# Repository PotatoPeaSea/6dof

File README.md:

# 6dofPCB — Virtual Flux (Product Requirements & Overview)

## 1. Product Vision
**Virtual Flux** is a high-fidelity, hardware-in-the-loop soldering simulator. It bridges physical motion and virtual physics to create a realistic training and evaluation environment for hand soldering. By using a physical 6DOF (Six Degrees of Freedom) robotic arm that acts as the soldering iron (currently in development, with full keyboard/mouse fallbacks available now), users can practice their technique on a virtual PCB rendered in a Unity desktop application. The simulation provides deterministic, physics-based reactions—including thermodynamics, flux activation, and solder wetting—coupled with real-time evaluation.

## 2. Target Audience & Use Cases
- **Soldering Trainees & Students**: Learn proper technique (angle, dwell time, temperature control, flux application) without consuming physical consumables or risking damage to expensive boards.
- **Instructors & Evaluators**: Provide standardized, objective, and deterministic grading of a student's soldering joints.
- **Hardware Enthusiasts**: Experiment with a novel hardware-software interface.

## 3. Core Features & Requirements (V1)

### 3.1 Physics & Simulation Engine
The core of Virtual Flux is its deterministic, grid-based simulation running at a fixed 5 ms timestep in Unity.
- **Thermal Model**: Heuristic exponential heat transfer from the iron tip to the pad, propagating across a grid.
- **Flux Dynamics**: Tracks states of flux (Cold -> Active -> Burnt) based on temperature thresholds. Flux cleans oxidation and enables solder flow.
- **Solder Flow & Wetting**: Grid-based solder deposition that flows to heated cells. Features visual metallic rendering and dynamic fillet capillary action morphing towards component pins.
- **Component Bonding**: Solderable pins detect solid vs. molten solder. A wetting reflow state machine ensures pins only bond if they contact molten solder that subsequently cools and solidifies.

### 3.2 User Interaction & Tooling
While the physical arm is the primary input, V1 supports full keyboard/mouse fallbacks.
- **6DOF Iron**: Translates and rotates in 3D space. Reports tip temperature and spatial pose.
- **Toolbelt**:
  - **Solder Wire**: Click-to-feed solder deposition.
  - **Flux Pen / Paste**: Apply flux to pads prior to heating.
  - **Tweezers**: Drag-and-drop SMD component placement (e.g., resistors) with snap-to-surface raycasting and kinematic stability.

### 3.3 Evaluation & HUD
- **Real-Time Guidance**: Dynamic UI panel tracking the active pad. Displays a collapsing step-by-step checklist (placement, flux, heat, solder, cool).
- **Deterministic Scoring**: Evaluates the joint based on strict tolerances:
  - Soldering angle (e.g., 40–55°)
  - Dwell time (e.g., 1.5–3 s)
  - Peak temperature (e.g., 250–360 °C)
  - Flux sequence (must flux before heating)
  - Solder volume and tip-feeding requirements.
- **Status & Latency**: Heads-up displays for iron temperature, active tool, board security status, and simulation frame timing.

## 4. System Architecture

The project is split into three tightly coupled domains:

### 4.1 Hardware (KiCad)
The physical 6DOF arm is driven by custom PCBs.
- **MCU Board**: The brains of the arm.
- **Controller Board**: Interfacing and power.
- *Located in `Hardware/` as KiCad 7+ projects and RS-274X Gerbers.*

### 4.2 Firmware (C/C++)
- **PlatformIO Project**: Runs on the MCU board. Solves arm kinematics and streams the tool tip's pose and temperature over USB-serial to the PC.
- *Located in `Firmware/6DoF Firmware/` (currently in progress).*
- *Protocol locked and documented in `docs/serial-protocol.md`.*

### 4.3 Software (Unity)
- **Unity 6 LTS (6000.0.x)** using the Universal Render Pipeline (URP) and the New Input System.
- Receives serial pose data (`P,x,y,z,pitch,yaw,roll,temp,seq`) and applies it to the virtual iron.
- Parses real Gerber files to generate the virtual copper PCB meshes.
- *Located in `Software/`.*

## 5. Repository Layout

| Path                | Contents                                                          |
|---------------------|-------------------------------------------------------------------|
| `Hardware/MCU/`     | MCU board — KiCad project + Gerbers. Lives on the arm itself.     |
| `Hardware/Controller/` | Controller board — KiCad project + Gerbers.                    |
| `Hardware/Gerbers/` | Zipped Gerber bundles for fabrication.                            |
| `Hardware/assets.pretty/` | Shared KiCad footprint library.                             |
| `Firmware/`         | PlatformIO firmware project for the 6DOF arm.                     |
| `Software/`         | Unity 6 LTS project. Open this folder in Unity Hub.               |
| `docs/`             | Cross-cutting docs — start with `serial-protocol.md`.             |
| `CLAUDE.md`         | Working agreement for AI coding assistants.                       |
| `NOTES.md`          | Session handoff log & historical milestones.                      |

## 6. Quick Start

1. **Hardware**: Open `Hardware/MCU/MCU.kicad_pro` or `Hardware/Controller/Controller.kicad_pro` in KiCad 7+.
2. **Software**: Open `Software/` in Unity 6 LTS. Load `Assets/Scenes/Workbench.unity` and press Play. See `Software/README.md` for detailed keyboard/mouse controls.

## 7. Future Roadmap (Post-V1)

- **Arm Firmware Completion**: Finish the C/C++ kinematics solver and hardware integration.
- **AI Joint-Quality Evaluation**: Machine learning models to assess the visual quality of the final solder fillet.
- **Advanced Hardware**: Haptic feedback, VR integration, and BLE wireless connectivity.

## License
TBD.

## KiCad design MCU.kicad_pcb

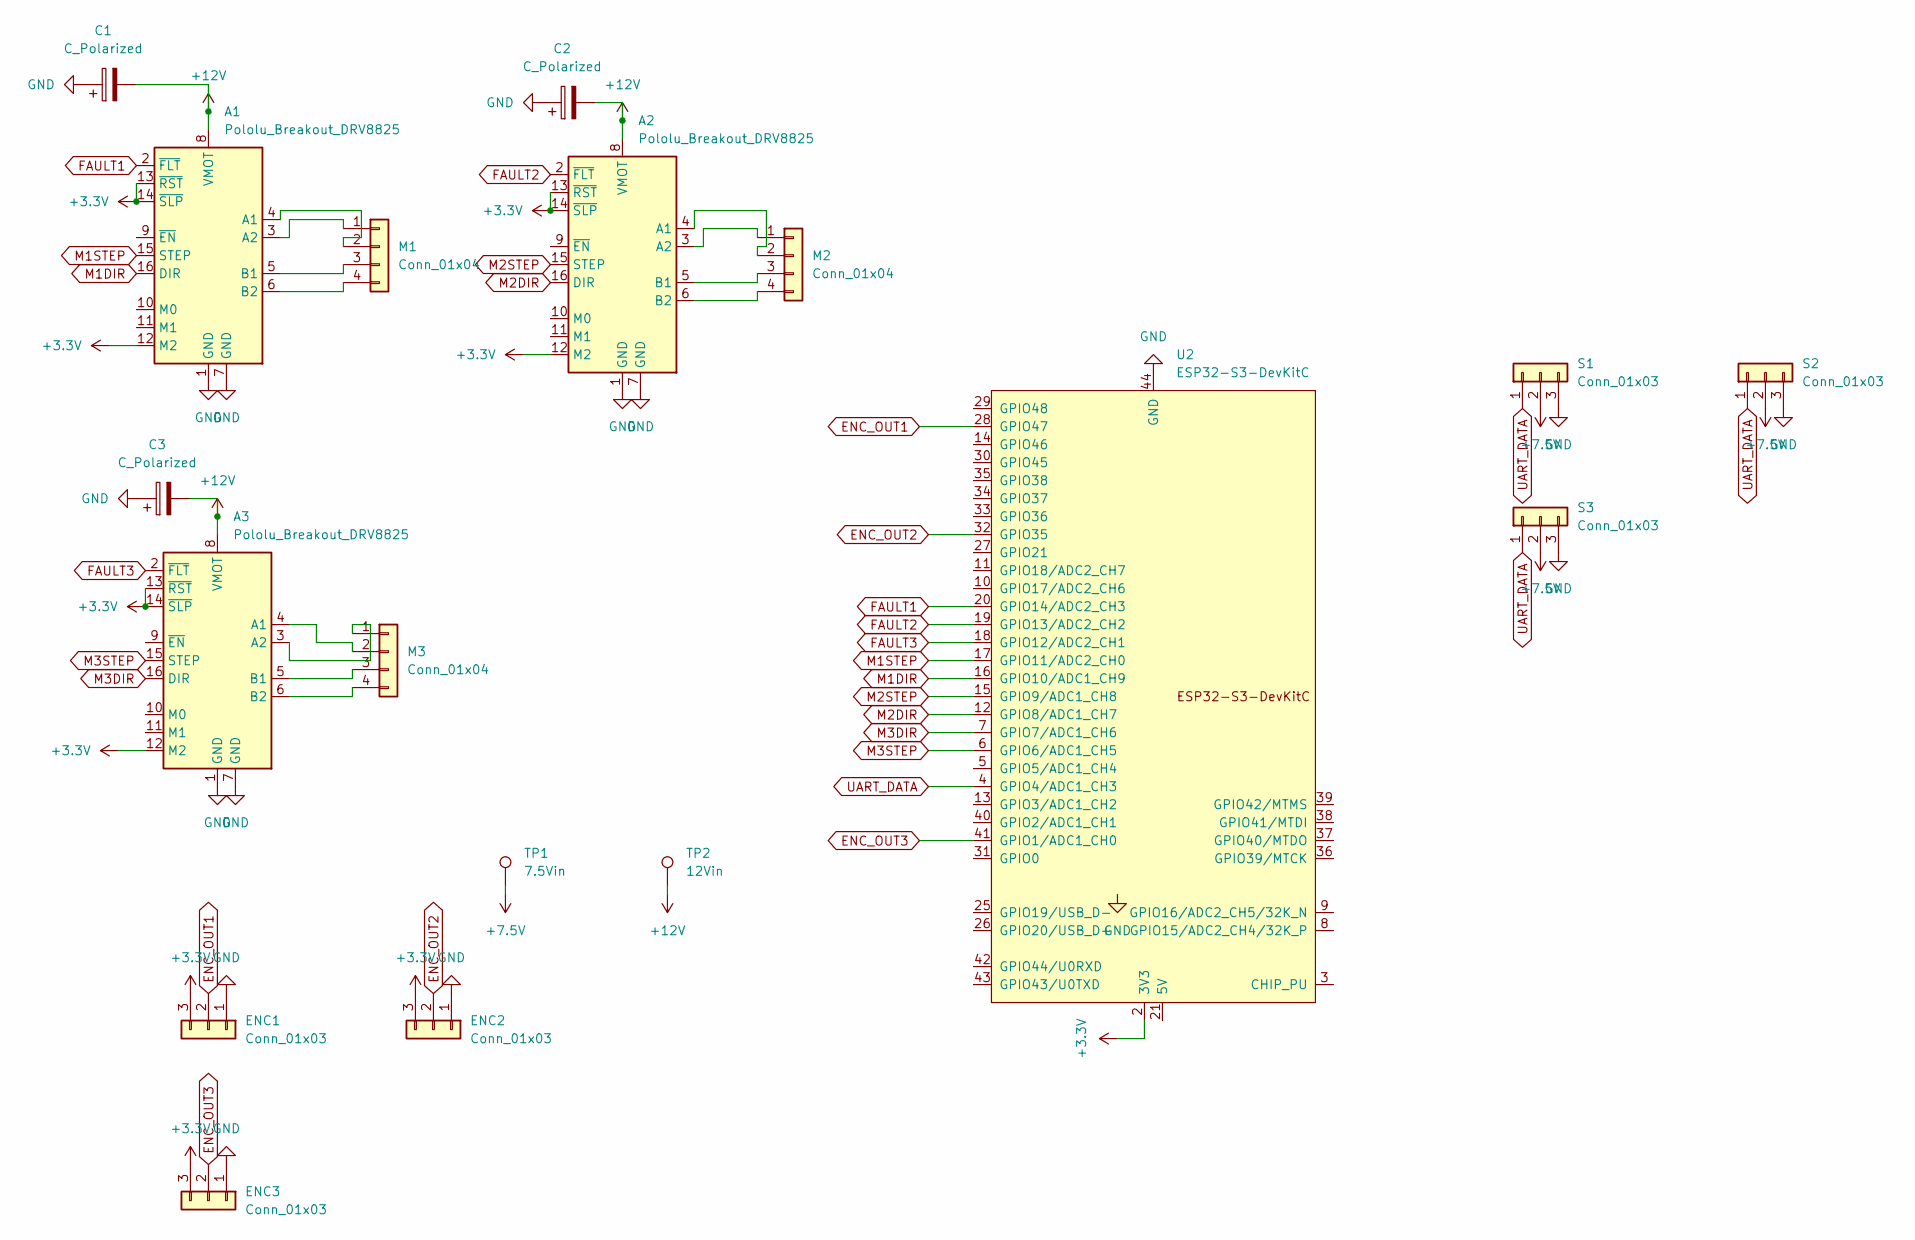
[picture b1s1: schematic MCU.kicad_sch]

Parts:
A1, A2, A3: Pololu_Breakout_DRV8825; Pololu_Breakout-16_15.2x20.3mm
C1, C2, C3: C_Polarized; CP_Radial_D6.3mm_P2.50mm
ENC1, ENC2, ENC3: Conn_01x03; PinHeader_1x03_P2.54mm_Vertical
M1, M2, M3: Conn_01x04; PinHeader_1x04_P2.54mm_Vertical
S1, S2, S3: Conn_01x03; JST_EH_B3B-EH-A_1x03_P2.50mm_Vertical
TP1: 7.5Vin; TestPoint_Plated_Hole_D5.0mm
TP2: 12Vin; TestPoint_Plated_Hole_D5.0mm
U2: ESP32-S3-DevKitC

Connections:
+3.3V: A1.12 (M2), A1.13 (~RST), A1.14 (~SLP), A2.12 (M2), A2.13 (~RST), A2.14 (~SLP), A3.12 (M2), A3.13 (~RST), A3.14 (~SLP), ENC1.3, ENC2.3, ENC3.3, U2.1 (3V3), U2.2 (3V3)
+7.5V: S1.2, S2.2, S3.2, TP1.1 (1_1)
+12V: A1.8 (VMOT), A2.8 (VMOT), A3.8 (VMOT), C1.2, C2.2, C3.2, TP2.1 (1_1)
ENC_OUT1: ENC1.2, U2.28 (GPIO47)
ENC_OUT2: ENC2.2, U2.32 (GPIO35)
ENC_OUT3: ENC3.2, U2.41 (GPIO1/ADC1_CH0)
FAULT1: A1.2 (~FLT), U2.20 (GPIO14/ADC2_CH3)
FAULT2: A2.2 (~FLT), U2.19 (GPIO13/ADC2_CH2)
FAULT3: A3.2 (~FLT), U2.18 (GPIO12/ADC2_CH1)
GND: A1.1 (GND), A1.7 (GND), A2.1 (GND), A2.7 (GND), A3.1 (GND), A3.7 (GND), C1.1, C2.1, C3.1, ENC1.1, ENC2.1, ENC3.1, S1.3, S2.3, S3.3, U2.22 (GND), U2.23 (GND), U2.24 (GND), U2.44 (GND)
M1DIR: A1.16 (DIR), U2.16 (GPIO10/ADC1_CH9)
M1STEP: A1.15 (STEP), U2.17 (GPIO11/ADC2_CH0)
M2DIR: A2.16 (DIR), U2.12 (GPIO8/ADC1_CH7)
M2STEP: A2.15 (STEP), U2.15 (GPIO9/ADC1_CH8)
M3DIR: A3.16 (DIR), U2.7 (GPIO7/ADC1_CH6)
M3STEP: A3.15 (STEP), U2.6 (GPIO6/ADC1_CH5)
unnamed: A1.4 (A1), M1.2
unnamed: A1.3 (A2), M1.1
unnamed: A1.5 (B1), M1.3
unnamed: A1.6 (B2), M1.4
unnamed: A2.4 (A1), M2.2
unnamed: A2.3 (A2), M2.1
unnamed: A2.5 (B1), M2.3
unnamed: A2.6 (B2), M2.4
unnamed: A3.4 (A1), M3.2
unnamed: A3.3 (A2), M3.1
unnamed: A3.5 (B1), M3.3
unnamed: A3.6 (B2), M3.4
UART_DATA: S1.1, S2.1, S3.1, U2.4 (GPIO4/ADC1_CH3)

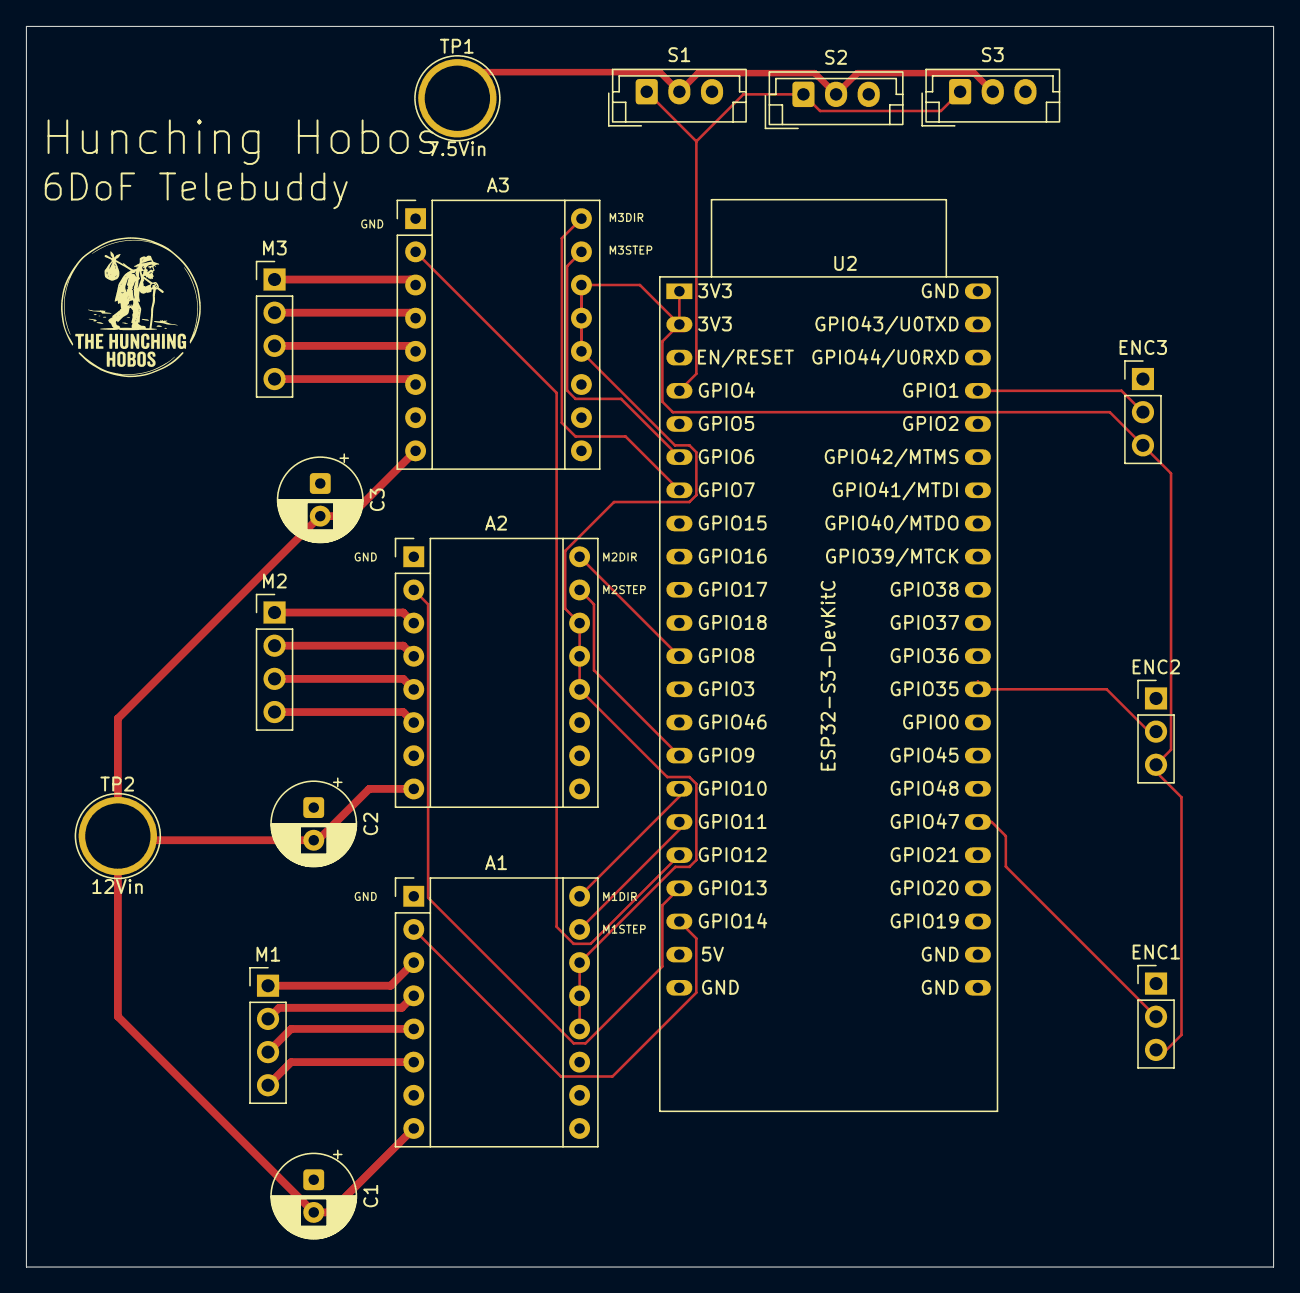
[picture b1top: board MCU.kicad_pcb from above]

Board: 2 copper layers, 95.5 x 95.0 mm, 18 parts (0 on the bottom side), 29 nets.

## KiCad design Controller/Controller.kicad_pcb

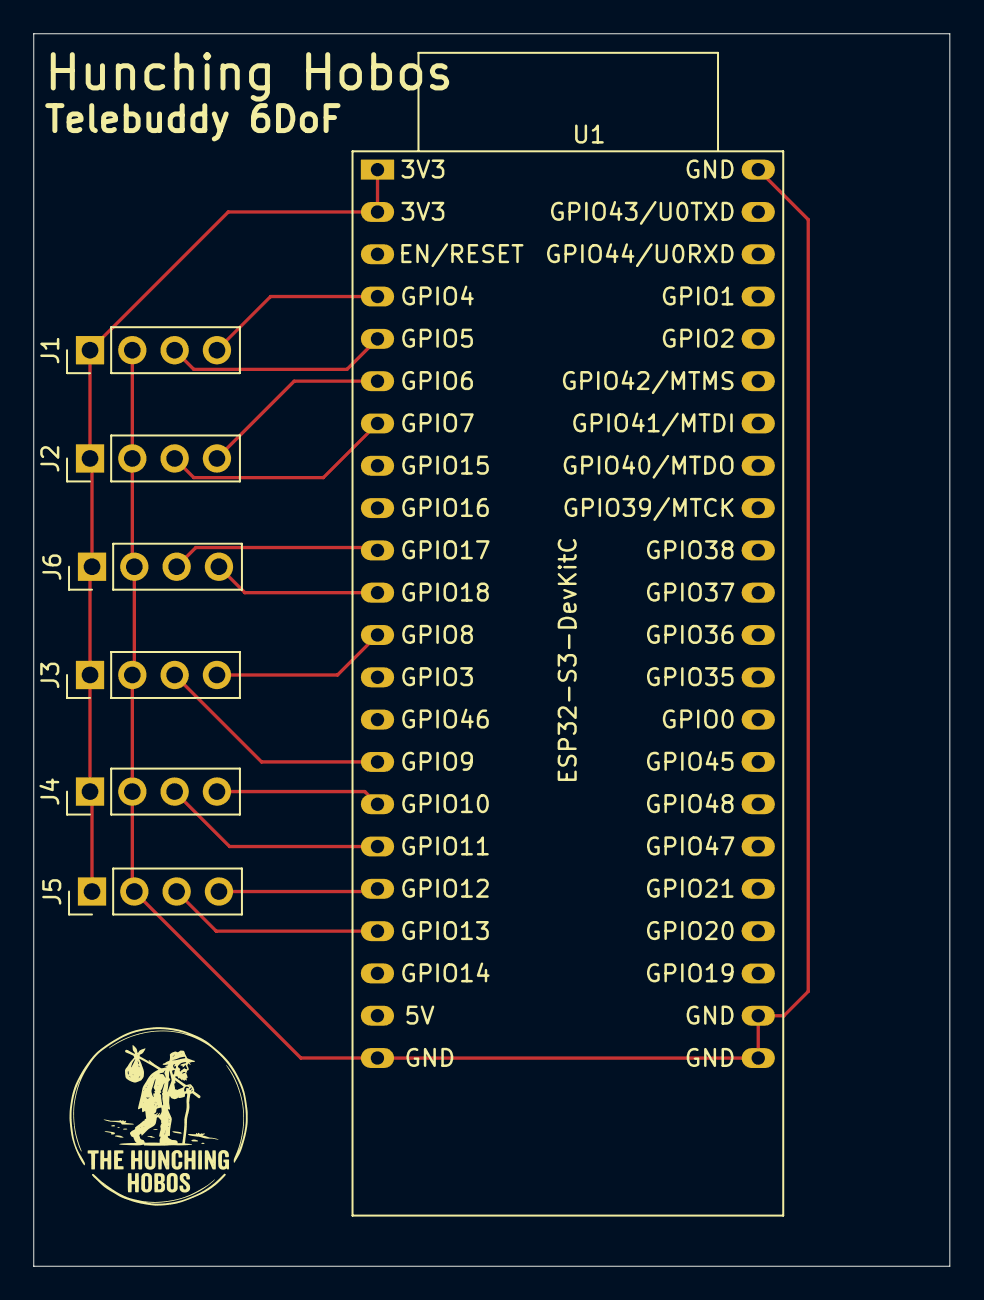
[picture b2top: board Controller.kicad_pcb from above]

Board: 2 copper layers, 55.0 x 74.0 mm, 7 parts (0 on the bottom side), 14 nets.

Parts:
J1, J2, J3, J4, J5, J6: Conn_01x04; PinHeader_1x04_P2.54mm_Vertical
U1: ESP32-S3-DevKitC

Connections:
+3.3V: J1.1, J2.1, J3.1, J4.1, J5.1, J6.1, U1.1 (3V3), U1.2 (3V3)
GND: J1.2, J2.2, J3.2, J4.2, J5.2, J6.2, U1.22 (GND), U1.23 (GND), U1.24 (GND), U1.44 (GND)
SCL1: J1.3, U1.5 (GPIO5/ADC1_CH4)
SCL2: J2.3, U1.7 (GPIO7/ADC1_CH6)
SCL3: J3.3, U1.15 (GPIO9/ADC1_CH8)
SCL4: J4.3, U1.17 (GPIO11/ADC2_CH0)
SCL5: J5.3, U1.19 (GPIO13/ADC2_CH2)
SCL6: J6.3, U1.10 (GPIO17/ADC2_CH6)
SDA1: J1.4, U1.4 (GPIO4/ADC1_CH3)
SDA2: J2.4, U1.6 (GPIO6/ADC1_CH5)
SDA3: J3.4, U1.12 (GPIO8/ADC1_CH7)
SDA4: J4.4, U1.16 (GPIO10/ADC1_CH9)
SDA5: J5.4, U1.18 (GPIO12/ADC2_CH1)
SDA6: J6.4, U1.11 (GPIO18/ADC2_CH7)

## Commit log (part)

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2026-05-26 Changed routings and added encoder ports (pwm output pins).
2026-05-26 finished trace wiring on PCB
2026-05-26 fixed trace widths
2026-05-27 completed board, ready for review, if passes review, ready to print
2026-05-27 forgot to add these
2026-05-27 changed logo footprint and capacitor spacing and labels
2026-05-27 created controller board and generated gerber files
2026-05-27 chore: restructure repo into Hardware/ + prep Software/ sibling
    Move all PCB sources (MCU project, Controller project, Gerbers, assets.pretty
    footprint library) under Hardware/. fp-lib-table relocated to Hardware/MCU/
    to preserve KiCad's "project-local table next to .kicad_pro" lookup, since
    the original layout had it next to the MCU project at root.
    Add Hardware/Firmware/ placeholder, top-level README.md, CLAUDE.md working
    agreement, and update .gitignore with the new MCU-backups path and the
2026-05-27 feat(software): bootstrap Unity simulator skeleton
    V1 Unity 6 LTS project under Software/ with:
    - Input layer: IIronInputSource interface, KeyboardIronInput driving 6DOF
    with WASD/QE/IJKL/JL/UO + Space, and SerialIronInput as a parser-only
    stub for the future arm firmware (wire format in docs/serial-protocol.md).
    - Hardware layer: IronController applies pose and ramps tip temperature.
    - Sim layer: ThermalModel (exact-exponential first-order), FluxModel
2026-05-27 fix(software/gerber): parser swallowed extended blocks after a newline
    The main parse loop only handled '%' and '*' as special; any other character
    (including the '\n' that always follows an extended block in KiCad output) was
    treated as the start of a regular block. That made the second '%...%' extended
    block on each line get consumed as part of a synthetic block whose body was
    "\n%MOIN" or "\n%ADDxx,...", which produced 0 apertures on real fab data.
    Skip whitespace between blocks before deciding whether we're at an extended
2026-05-27 feat(software): wire up V1 — zip loader, sim driver, status HUD, solder-volume rule
    Fills the gaps between the V1 skeleton and a scene that actually plays.
    - GerberZipReader: pure-IO helper that picks F_Cu (then B_Cu, then any .gbr)
    out of a KiCad-exported zip bundle. GerberLoadUI now routes both bare and
    zipped paths through it.
    - ToolBelt: emits FluxApplied / SolderFed deposition events so the evaluator
    can observe process order from outside.
2026-05-27 test(software): EditMode tests + standalone .NET runner for pure-logic paths
    The Unity-side test runner (NUnit + ScriptableObject + MonoBehaviour) is the
    canonical authority for these tests. The standalone runner is a parallel
    validation harness that compiles a subset of the source against minimal
    UnityEngine shims so we can exercise pure-logic paths (parser, zip reader,
    thermal/flux/flow models, evaluator scoring) without a Unity install — which
    is what made it possible to find the parser whitespace bug from the previous
2026-06-03 added firmware
2026-06-03 changed as5600 initialization to fix initialization bug that was creating i2c conflict
2026-06-03 workbench builder
2026-06-04 safe point with multi pads
2026-06-04 components, flux, and guidance
2026-06-10 Update READMEs to reflect current project state
2026-06-10 Align CLAUDE.md and README.md with new Firmware structure
2026-06-10 docs: rewrite README.md as PRD
2026-06-10 Address PRD review comments
2026-06-22 Squashed 'Hardware/CAD/3-phase-cycloid/' content from commit 95cee1a
    git-subtree-dir: Hardware/CAD/3-phase-cycloid
    git-subtree-split: 95cee1a611d9baad6a0d7096d495dd2442eb613d
